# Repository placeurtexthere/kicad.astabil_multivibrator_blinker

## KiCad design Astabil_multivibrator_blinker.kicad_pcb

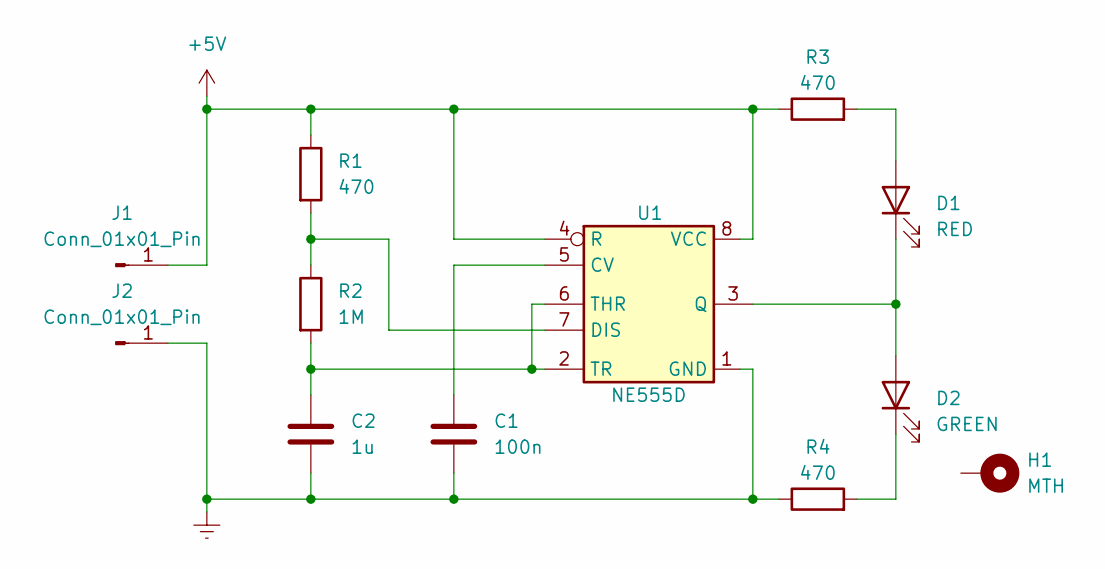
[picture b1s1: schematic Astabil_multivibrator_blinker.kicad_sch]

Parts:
C1: 100n; C_0603_1608Metric_Pad1.08x0.95mm_HandSolder
C2: 1u; C_0603_1608Metric_Pad1.08x0.95mm_HandSolder
D1: RED; LED_1206_3216Metric_Pad1.42x1.75mm_HandSolder
D2: GREEN; LED_1206_3216Metric_Pad1.42x1.75mm_HandSolder
H1: MTH; MountingHole_4mm_Pad_Via
J1, J2: Conn_01x01_Pin; PinSocket_1x01_P2.00mm_Horizontal
R1, R3, R4: 470; R_0805_2012Metric_Pad1.20x1.40mm_HandSolder
R2: 1M; R_0805_2012Metric_Pad1.20x1.40mm_HandSolder
U1: NE555D; SOIC-8_3.9x4.9mm_P1.27mm

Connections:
+5V: J1.1, R1.1, R3.1, U1.4 (R), U1.8 (VCC)
Earth: C1.2, C2.2, J2.1, R4.1, U1.1 (GND)
unnamed: D1.2 (A), R3.2
unnamed: D1.1 (K), D2.2 (A), U1.3 (Q)
unnamed: D2.1 (K), R4.2
unnamed: C1.1, U1.5 (CV)
unnamed: R1.2, R2.1, U1.7 (DIS)
unnamed: C2.1, R2.2, U1.2 (TR), U1.6 (THR)

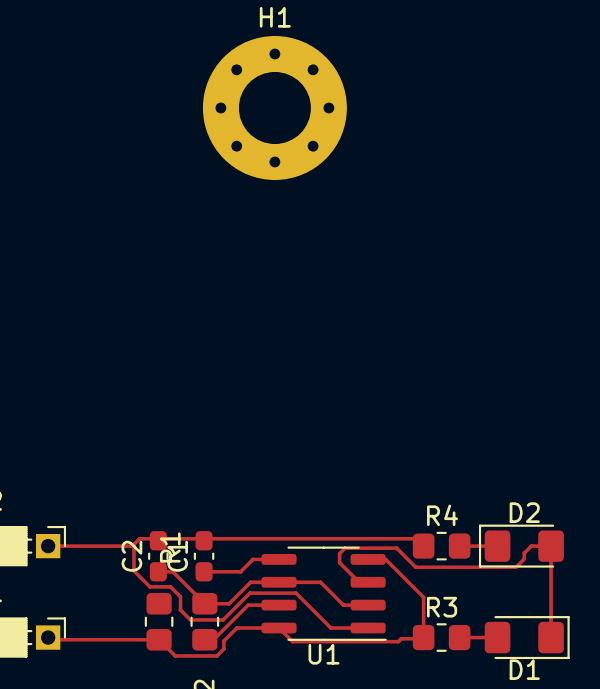
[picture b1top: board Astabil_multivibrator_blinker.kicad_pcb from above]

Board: 2 copper layers, 12 parts (0 on the bottom side), 8 nets.

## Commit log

2023-10-28 Updated files
